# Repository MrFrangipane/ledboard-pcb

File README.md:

# LED Board - PCB

v1 January 2024

This project works with
- [LED Board - Firmware minimal](https://github.com/MrFrangipane/ledboard-firmware-minimal)
- [LED Board - Desktop minimal](https://github.com/MrFrangipane/ledboard-desktop-minimal)
- [LED Board - Firmware full](https://github.com/MrFrangipane/ledboard-firmware-full)
- [LED Board - Desktop full](https://github.com/MrFrangipane/ledboard-desktop-full)

## Main board

ArtNet to LED strips (x8 RS485 transmitters)

- Raspberry Pi Pico

- ENC28J60 SPI module

- Front panel for screen, rotary encoder, push button

## Receiver  (x8)

RS485 to LED strip

## Schematics

## Gerbers

- Edge Cuts

- F Cu

- In1 Cu

- In2 Cu

- B Cu

- F Silkscreen

- B Silkscreen

- F Paste

- B Paste

- F Mask

- B Mask

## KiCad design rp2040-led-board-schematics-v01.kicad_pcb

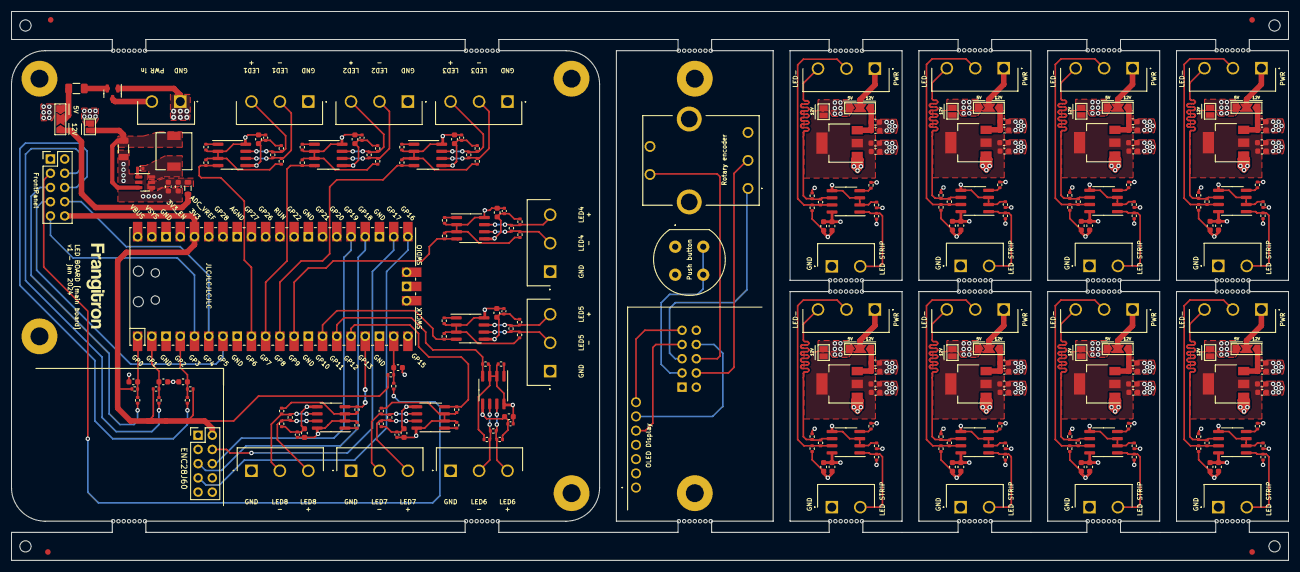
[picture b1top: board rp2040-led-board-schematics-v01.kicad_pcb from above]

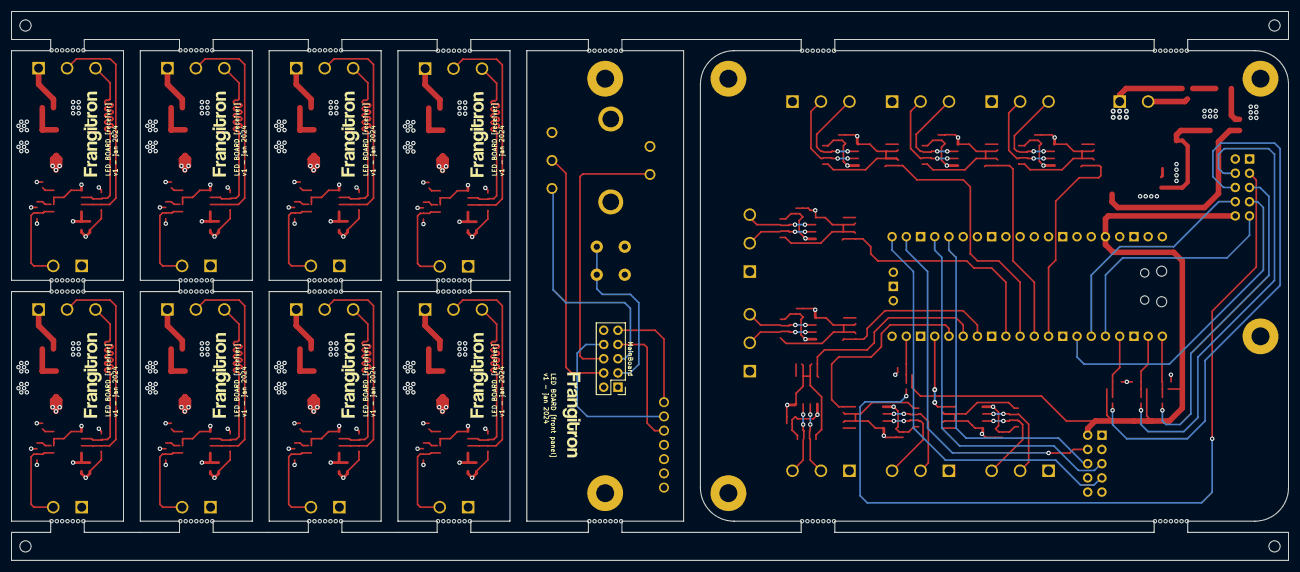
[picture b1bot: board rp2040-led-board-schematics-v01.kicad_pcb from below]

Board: 4 copper layers, 228.0 x 98.0 mm, 293 parts (10 on the bottom side), 139 nets.

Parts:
C1, C2, C3, C10, C12, C13, C14, C15, C19, C21, C24, C25, C29, C30, C31, C32, C38, C39, C40, C41, C47, C50, C52, C53: 10uF; C_0603_1608Metric
C4, C7, C8, C18, C28, C43, C44, C46: 10uF; C_0402_1005Metric
C5, C6, C9, C17, C20, C22, C23, C26, C27, C33, C34, C35, C36, C37, C42, C45, C48, C49, C51, C54, C55, C56, C57, C58, C59, C60, C61, C62, C63, C64, C65, C66, C67, C68, C69, C70, C71: 100nF; C_0603_1608Metric
C11: 1uF; C_0603_1608Metric
C72: 100nF; C_0402_1005Metric
C74: 10uF; C_1206_3216Metric
DS1: NHD-0216AW-IB3; NewHaven-OLED-NHD-0216AW-IB3
F1: 1A; Fuse_1206_3216Metric
FB2: 600 @ 600Mhz; L_0805_2012Metric
FM1, FM2, FM3, FM4: Fiducial; Fiducial_1mm_Mask2mm
H1, H2, H32, H33: MountingHole; MountingHole_2mm
H3, H4, H5, H6, H7, H8, H9, H14, H15, H16, H17, H18, H19, H20, H21, H25, H26, H27, H28, H29, H30, H31: mouse-bites-1x07-jlc
H10, H11, H12, H22, H23, H24: MountingHole_Pad; MountingHole_3.2mm_M3_Pad
H13, H34, H35, H36, H37, H38, H39, H40, H41, H42: frangitron_logo_16mm
J1, J2, J3, J4, J15, J16, J17, J18: ReceiverRS485; ScrewTerminal_01x03_5.08_Amphenol
J5: PWR_IN; ScrewTerminal_01x02_5.08_Amphenol
J6, J7, J8, J10, J19, J20, J21, J22: Terminal; ScrewTerminal_01x03_5.08_Amphenol
J9: FrontPanel; PinHeader_2x05_P2.54mm_Vertical
J11, J12, J13, J14, J23, J24, J25, J26: ReceiverData; ScrewTerminal_01x02_5.08_Amphenol
J27: MainBoard; PinHeader_2x05_P2.54mm_Vertical
JP1, JP2, JP3, JP4, JP10, JP11, JP12, JP13, JP14: 1-2 12V; SolderJumper-3_P2.0mm_Open_TrianglePad1.0x1.5mm_NumberLabels
JP5, JP6, JP7, JP8, JP9, JP15, JP16, JP17, JP18: 12V; SolderJumper-2_P1.3mm_Open_Pad1.0x1.5mm
L1: 5.6mH; L_6.3x6.3_H3
Q1: AO3401A; SOT-23
R1, R2, R5, R6, R11, R12, R17, R19, R21, R23, R24, R28, R29, R32, R33, R36, R37, R40, R41, R42, R45, R46, R50, R51, R62, R65, R67, R69, R76, R77, R81, R82, R86, R87, R91, R92, R93, R94, R95, R96: 10K; R_0402_1005Metric
R3, R10, R13, R27, R31, R34, R39, R44, R48, R60, R64, R72, R75, R78, R84, R90: 120; R_0402_1005Metric
R4, R7, R8, R9, R14, R15, R16, R18, R20, R22, R25, R26, R30, R35, R38, R43, R47, R49, R61, R63, R66, R68, R70, R71, R73, R74, R79, R80, R83, R85, R88, R89: 20K; R_0402_1005Metric
R52, R53, R54, R56: 10k; R_0402_1005Metric
R55, R57, R58, R59: 1k; R_0402_1005Metric
SW1: PEC16; PEC164120FS0012
SW2: Button; C&K_PushButtonSwitch_SPST_D6C90F2LFS
U2: LMR50410Y5FQDBVRQ1; SOT-23-6
U6, U7, U8, U9, U10, U11, U12, U13, U15, U16, U21, U22, U23, U24, U25, U26: MAX485EE; SOIC-8_3.9x4.9mm_P1.27mm
U14: Pico; RPi_Pico_SMD_TH
U17, U29, U30, U31, U32, U33, U34, U35: AMS1117-5.0; SOT-223-3_TabPin2
U27: ENC28J60; ENC28J60-SPI-Ethernet-Module

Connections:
+3V3: J9.10, R52.1, R53.1, R54.1, R56.1, U14.36 (3V3), U27.9 (VCC)
+5V: C4.1, C5.1, C6.1, C7.1, C8.1, C9.1, C17.1, C18.1, C27.1, C28.1, C37.1, C42.1, C43.1, C44.1, C45.1, C46.1, JP5.2 (B), JP10.3 (B), R1.1, R2.1, R4.1, R5.1, R6.1, R9.1, R11.1, R12.1, R15.1, R24.1, R42.1, R43.1, R45.1, R46.1, R47.1, R50.1, R51.1, R61.1, R62.1, R63.1, R65.1, R67.1, R69.1, R71.1, U6.2 (~RE), U6.3 (DE), U6.8 (VCC), U7.2 (~RE), U7.3 (DE), U7.8 (VCC), U8.2 (~RE), U8.3 (DE), U8.8 (VCC), U13.2 (~RE), U13.3 (DE), U13.8 (VCC), U14.39 (VSYS), U15.2 (~RE), U15.3 (DE), U15.8 (VCC), U16.2 (~RE), U16.3 (DE), U16.8 (VCC), U21.2 (~RE), U21.3 (DE), U21.8 (VCC), U22.2 (~RE), U22.3 (DE), U22.8 (VCC)
+12V: FB2.1, JP10.1 (A)
/Buck in: C11.1, C71.1, FB2.2, U2.4 (EN), U2.5 (VIN)
/Buck out: C74.1, JP5.1 (A), L1.2, U2.3 (FB)
/CB: C72.2, U2.1 (CB)
/FP +3V3: DS1.2 (VDD_SEL), DS1.3 (VDDIO), J27.10
/FP GND: DS1.1 (GND), DS1.4 (SA0), H12.1, H24.1, J27.1, SW1.C1, SW1.E1, SW2.1, SW2.2
/LED to RS485 1/D+: J6.3, R3.1, R7.1, U6.7 (B)
/LED to RS485 1/D-: J6.2, R3.2, R4.2, U6.6 (A)
/LED to RS485 2/D+: J7.3, R8.1, R10.1, U7.7 (B)
/LED to RS485 2/D-: J7.2, R9.2, R10.2, U7.6 (A)
/LED to RS485 3/D+: J8.3, R13.1, R14.1, U8.7 (B)
/LED to RS485 3/D-: J8.2, R13.2, R15.2, U8.6 (A)
/LED to RS485 4/D+: J10.3, R25.1, R44.1, U13.7 (B)
/LED to RS485 4/D-: J10.2, R43.2, R44.2, U13.6 (A)
/LED to RS485 5/D+: J19.3, R48.1, R49.1, U15.7 (B)
/LED to RS485 5/D-: J19.2, R47.2, R48.2, U15.6 (A)
/LED to RS485 6/D+: J22.3, R70.1, R72.1, U16.7 (B)
/LED to RS485 6/D-: J22.2, R71.2, R72.2, U16.6 (A)
/LED to RS485 7/D+: J21.3, R64.1, R68.1, U22.7 (B)
/LED to RS485 7/D-: J21.2, R63.2, R64.2, U22.6 (A)
/LED to RS485 8/D+: J20.3, R60.1, R66.1, U21.7 (B)
/LED to RS485 8/D-: J20.2, R60.2, R61.2, U21.6 (A)
/Receiver 1/5V: C47.1, C48.1, JP11.3 (B), JP15.1 (A), R73.1, R76.1, R77.1, R93.1, U23.8 (VCC)
/Receiver 1/12V: C29.1, C55.1, JP11.1 (A), U17.3 (VI)
/Receiver 1/D+: J15.2, R74.1, R75.1, U23.7 (B)
/Receiver 1/D-: J15.3, R73.2, R75.2, U23.6 (A)
/Receiver 1/DATA: J23.2, R93.2, U23.1 (RO)
/Receiver 1/GND: C29.2, C38.2, C47.2, C48.2, C55.2, C63.2, J23.1, R74.2, R77.2, U17.1 (GND), U23.2 (~RE), U23.3 (DE), U23.5 (GND)
/Receiver 1/LDO OUT: C38.1, C63.1, JP15.2 (B), U17.2 (VO)
/Receiver 1/PWR IN: J15.1, JP11.2 (C)
/Receiver 2/5V: C19.1, C20.1, JP1.3 (B), JP6.1 (A), R16.1, R17.1, R28.1, R29.1, U9.8 (VCC)
/Receiver 2/12V: C10.1, C56.1, JP1.1 (A), U29.3 (VI)
/Receiver 2/D+: J1.2, R26.1, R27.1, U9.7 (B)
/Receiver 2/D-: J1.3, R16.2, R27.2, U9.6 (A)
/Receiver 2/DATA: J11.2, R29.2, U9.1 (RO)
/Receiver 2/GND: C10.2, C12.2, C19.2, C20.2, C56.2, C64.2, J11.1, R26.2, R28.2, U9.2 (~RE), U9.3 (DE), U9.5 (GND), U29.1 (GND)
/Receiver 2/LDO OUT: C12.1, C64.1, JP6.2 (B), U29.2 (VO)
/Receiver 2/PWR IN: J1.1, JP1.2 (C)
/Receiver 3/5V: C49.1, C50.1, JP12.3 (B), JP16.1 (A), R79.1, R81.1, R82.1, R94.1, U24.8 (VCC)
/Receiver 3/12V: C30.1, C57.1, JP12.1 (A), U30.3 (VI)
/Receiver 3/D+: J16.2, R78.1, R80.1, U24.7 (B)
/Receiver 3/D-: J16.3, R78.2, R79.2, U24.6 (A)
/Receiver 3/DATA: J24.2, R94.2, U24.1 (RO)
/Receiver 3/GND: C30.2, C39.2, C49.2, C50.2, C57.2, C65.2, J24.1, R80.2, R81.2, U24.2 (~RE), U24.3 (DE), U24.5 (GND), U30.1 (GND)
/Receiver 3/LDO OUT: C39.1, C65.1, JP16.2 (B), U30.2 (VO)
/Receiver 3/PWR IN: J16.1, JP12.2 (C)
/Receiver 4/5V: C21.1, C22.1, JP2.3 (B), JP7.1 (A), R18.1, R19.1, R32.1, R33.1, U10.8 (VCC)
/Receiver 4/12V: C1.1, C58.1, JP2.1 (A), U31.3 (VI)
/Receiver 4/D+: J2.2, R30.1, R31.1, U10.7 (B)
/Receiver 4/D-: J2.3, R18.2, R31.2, U10.6 (A)
/Receiver 4/DATA: J12.2, R32.2, U10.1 (RO)
/Receiver 4/GND: C1.2, C13.2, C21.2, C22.2, C58.2, C66.2, J12.1, R30.2, R33.2, U10.2 (~RE), U10.3 (DE), U10.5 (GND), U31.1 (GND)
/Receiver 4/LDO OUT: C13.1, C66.1, JP7.2 (B), U31.2 (VO)
/Receiver 4/PWR IN: J2.1, JP2.2 (C)
/Receiver 5/5V: C51.1, C52.1, JP13.3 (B), JP17.1 (A), R83.1, R86.1, R87.1, R95.1, U25.8 (VCC)
/Receiver 5/12V: C31.1, C59.1, JP13.1 (A), U32.3 (VI)
/Receiver 5/D+: J17.2, R84.1, R85.1, U25.7 (B)
/Receiver 5/D-: J17.3, R83.2, R84.2, U25.6 (A)
/Receiver 5/DATA: J25.2, R95.2, U25.1 (RO)
/Receiver 5/GND: C31.2, C40.2, C51.2, C52.2, C59.2, C67.2, J25.1, R85.2, R86.2, U25.2 (~RE), U25.3 (DE), U25.5 (GND), U32.1 (GND)
/Receiver 5/LDO OUT: C40.1, C67.1, JP17.2 (B), U32.2 (VO)
/Receiver 5/PWR IN: J17.1, JP13.2 (C)
/Receiver 6/5V: C23.1, C24.1, JP3.3 (B), JP8.1 (A), R20.1, R21.1, R36.1, R37.1, U11.8 (VCC)
/Receiver 6/12V: C2.1, C60.1, JP3.1 (A), U33.3 (VI)
/Receiver 6/D+: J3.2, R34.1, R35.1, U11.7 (B)
/Receiver 6/D-: J3.3, R20.2, R34.2, U11.6 (A)
/Receiver 6/DATA: J13.2, R37.2, U11.1 (RO)
/Receiver 6/GND: C2.2, C14.2, C23.2, C24.2, C60.2, C68.2, J13.1, R35.2, R36.2, U11.2 (~RE), U11.3 (DE), U11.5 (GND), U33.1 (GND)
/Receiver 6/LDO OUT: C14.1, C68.1, JP8.2 (B), U33.2 (VO)
/Receiver 6/PWR IN: J3.1, JP3.2 (C)
/Receiver 7/5V: C53.1, C54.1, JP14.3 (B), JP18.1 (A), R89.1, R91.1, R92.1, R96.1, U26.8 (VCC)
/Receiver 7/12V: C32.1, C61.1, JP14.1 (A), U34.3 (VI)
/Receiver 7/D+: J18.2, R88.1, R90.1, U26.7 (B)
/Receiver 7/D-: J18.3, R89.2, R90.2, U26.6 (A)
/Receiver 7/DATA: J26.2, R96.2, U26.1 (RO)
/Receiver 7/GND: C32.2, C41.2, C53.2, C54.2, C61.2, C69.2, J26.1, R88.2, R92.2, U26.2 (~RE), U26.3 (DE), U26.5 (GND), U34.1 (GND)
/Receiver 7/LDO OUT: C41.1, C69.1, JP18.2 (B), U34.2 (VO)
/Receiver 7/PWR IN: J18.1, JP14.2 (C)
/Receiver 8/5V: C25.1, C26.1, JP4.3 (B), JP9.1 (A), R22.1, R23.1, R40.1, R41.1, U12.8 (VCC)
/Receiver 8/12V: C3.1, C62.1, JP4.1 (A), U35.3 (VI)
/Receiver 8/D+: J4.2, R38.1, R39.1, U12.7 (B)
/Receiver 8/D-: J4.3, R22.2, R39.2, U12.6 (A)
/Receiver 8/DATA: J14.2, R40.2, U12.1 (RO)
/Receiver 8/GND: C3.2, C15.2, C25.2, C26.2, C62.2, C70.2, J14.1, R38.2, R41.2, U12.2 (~RE), U12.3 (DE), U12.5 (GND), U35.1 (GND)
/Receiver 8/LDO OUT: C15.1, C70.1, JP9.2 (B), U35.2 (VO)
/Receiver 8/PWR IN: J4.1, JP4.2 (C)
/SW: C72.1, L1.1, U2.6 (SW)
FPDisplayRST: DS1.7 (~RES), J27.9
FPDisplaySCL: DS1.5 (SCL), J27.7
FPDisplaySDA: DS1.6 (SDA), J27.8
FPEncoderA: J27.5, SW1.A1
FPEncoderB: J27.4, SW1.B1
FPEncoderS: J27.6, SW1.D1
FPSwitchPush: J27.3, SW2.3 (K), SW2.4 (A)
GND: C4.2, C5.2, C6.2, C7.2, C8.2, C9.2, C11.2, C17.2, C18.2, C27.2, C28.2, C33.2, C34.2, C35.2, C36.2, C37.2, C42.2, C43.2, C44.2, C45.2, C46.2, C71.2, C74.2, H10.1, H11.1, H22.1, H23.1, J5.1, J6.1, J7.1, J8.1, J9.1, J10.1, J19.1, J20.1, J21.1, J22.1, Q1.1 (G), R7.2, R8.2, R14.2, R25.2, R49.2, R66.2, R68.2, R70.2, U2.2 (GND), U6.5 (GND), U7.5 (GND), U8.5 (GND), U13.5 (GND), U14.3 (GND), U14.8 (GND), U14.13 (GND), U14.18 (GND), U14.23 (GND), U14.28 (GND), U14.42 (GND), U15.5 (GND), U16.5 (GND), U21.5 (GND), U22.5 (GND), U27.10 (GND)
LED1 out: R1.2, U6.4 (DI), U14.9 (GPIO6)
LED2 out: R5.2, U7.4 (DI), U14.10 (GPIO7)
LED3 out: R11.2, U8.4 (DI), U14.11 (GPIO8)
LED4 out: R42.2, U13.4 (DI), U14.12 (GPIO9)
LED5 out: R46.2, U14.14 (GPIO10), U15.4 (DI)
LED6 out: R51.2, U14.15 (GPIO11), U16.4 (DI)
LED7 out: R65.2, U14.16 (GPIO12), U22.4 (DI)
LED8 out: R62.2, U14.17 (GPIO13), U21.4 (DI)
MBEncoderA: J9.5, R58.2
MBEncoderB: J9.4, R57.2
MBEncoderS: J9.6, R59.1
MBSwitchPush: J9.3, R55.2
MCUDisplayRST: J9.9, U14.5 (GPIO3)
MCUDisplaySCL: J9.7, U14.7 (GPIO5)
MCUDisplaySDA: J9.8, U14.6 (GPIO4)
MCUEncoderA: C33.1, R52.2, R58.1, U14.1 (GPIO0)
MCUEncoderB: C34.1, R53.2, R57.1, U14.2 (GPIO1)
MCUEncoderS: C35.1, R54.2, R59.2, U14.4 (GPIO2)
MCUSwitchPush: C36.1, R55.1, R56.2, U14.19 (GPIO14)
unnamed: J5.2, Q1.3 (D)
unnamed: F1.1, JP10.2 (C)
unnamed: F1.2, Q1.2 (S)
unnamed: R2.2, U6.1 (RO)
unnamed: R6.2, U7.1 (RO)
unnamed: R12.2, U8.1 (RO)
unnamed: R17.2, U9.4 (DI)
unnamed: R19.2, U10.4 (DI)
unnamed: R21.2, U11.4 (DI)
unnamed: R23.2, U12.4 (DI)
unnamed: R24.2, U13.1 (RO)
unnamed: R45.2, U15.1 (RO)
unnamed: R50.2, U16.1 (RO)
unnamed: R67.2, U21.1 (RO)
unnamed: R69.2, U22.1 (RO)
unnamed: R76.2, U23.4 (DI)
unnamed: R82.2, U24.4 (DI)
unnamed: R87.2, U25.4 (DI)
unnamed: R91.2, U26.4 (DI)
PI spi0 CSn: U14.22 (GPIO17), U27.7 (CS)
PI spi0 RX: U14.21 (GPIO16), U27.4 (SO)
PI spi0 SCK: U14.24 (GPIO18), U27.6 (SCK)
PI spi0 TX: U14.25 (GPIO19), U27.5 (SI)

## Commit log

2024-01-11 add svg
2024-01-12 footprints ok
2024-01-12 start Phil's Lab tutorial
2024-01-13 main board PCB done (needs checking)
2024-01-14 fix ENC module dimensions + adapt pcb accordingly
2024-01-14 1st panel test, before cloning 8 receivers
2024-01-14 receiver layout OK, some references fixed
2024-01-15 OK for first fabrication review
2024-01-15 fix readme svg filename
2024-01-15 unify receiver layout, reduce global heigt by 1mm for symmetry
2024-01-15 panelization with only mouse bites, routing finished
2024-01-15 resize front panel, fix header orientation, fix receivers layouts and footprints
2024-01-15 Geographically reannotate
2024-01-16 fix power sources, update reveivers accordingly (main board PCB not updated yet)
2024-01-16 should be ready to find parts
2024-01-16 fix: update .svg & .png files, correct some silkscreen details
2024-01-16 fix: DRC & ERC revealed designators were out of sync between schem and pcb
2024-01-16 JLCPCB pluging assignation done
2024-01-17 order placed
2024-01-17 rename to v1 (to match silkscreen), improve readme and schematics layouts
2024-01-17 add gerbers to readme
2024-01-18 remove designators from silkscreens (manufacturer considers different designs otherwise)
2024-01-18 fix: remove designators from silkscreens (forgot some)
